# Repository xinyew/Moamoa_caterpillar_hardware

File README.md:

# Caterpillar — Hardware

KiCad project for the **caterpillar** board: a custom nRF54L15-based motor-control + IMU
board (vibration robot). Firmware lives in a sibling repo:
`Moamoa_caterpillar_firmware` (Zephyr / nRF Connect SDK v3.3.0, board target
`caterpillar/nrf54l15/cpuapp`).

## Board overview

| Subsystem    | IC                           | Interface   | Purpose                                     |
| ------------ | ---------------------------- | ----------- | ------------------------------------------- |
| MCU + BLE    | Raytac AN54LQ-P15 (nRF54L15) | —          | Application core + BLE remote control       |
| Motor driver | DRV8212P                     | PWM + GPIO  | Dual-channel motor control                  |
| Digital pot  | MAX5419LETA                  | I2C`0x28` | Adjusts motor supply voltage via STBB1-APUR |
| Buck-boost   | STBB1-APUR                   | GPIO enable | Motor supply rail                           |
| Buck-boost   | ADP2503 (3.3 V)              | —          | Logic supply rail                           |
| IMU          | ASM330LHHTR                  | SPI         | 6-axis accel/gyro                           |
| Inductor     | TDK VLCF4020T-2R2N1R7        | —          | 2.2 µH power inductor                      |

## Pin map (must stay in sync with firmware)

| Signal         | Pin   | Dir   | Notes                               |
| -------------- | ----- | ----- | ----------------------------------- |
| I2C SDA        | P1.02 | bidir | Digipot only (`i2c20`)            |
| I2C SCL        | P1.03 | out   | Digipot only                        |
| IMU INT1       | P1.04 | in    | ASM330LHHTR data-ready              |
| IMU INT2       | P1.05 | in    | ASM330LHHTR secondary interrupt     |
| SPI CS         | P1.09 | out   | ASM330LHHTR chip select, active-low |
| SPI SCLK       | P1.10 | out   | IMU SPI clock                       |
| SPI MOSI       | P1.13 | out   | IMU SPI data out (U2 SDI)           |
| SPI MISO       | P1.14 | in    | IMU SPI data in (U2 SDO)            |
| STATUS LED     | P0.01 | out   | Blue LED via 470R, active-high      |
| DRV8212 ~SLEEP | P1.06 | out   | Active-low sleep (LOW = sleep)      |
| PWM IN1        | P1.07 | out   | Motor driver channel 1 (`pwm20`)  |
| PWM IN2        | P1.08 | out   | Motor driver channel 2              |
| DCDC EN        | P2.03 | out   | STBB1-APUR enable, active-high      |

If you change any of these nets, update the devicetree in the firmware repo
(`boards/kamoamoa/caterpillar/`) and this table.

## Project files

```
caterpillar.kicad_pro   project settings
caterpillar.kicad_sch   schematic
caterpillar.kicad_pcb   PCB layout
caterpillar.csv         BOM export
sym-lib-table           project symbol libraries
fp-lib-table            project footprint libraries
library/                custom components (see rules below)
```

`caterpillar.kicad_prl` and `fp-info-cache` are per-user/cache files and are gitignored.

## Library component organization — the rules

Every custom component lives in its own folder under `library/`, laid out exactly like this:

```
library/<PART>/
  <PART>.kicad_sym          symbol library (named after the part, no dated filenames)
  footprints.pretty/        footprint library (one .kicad_mod per footprint variant)
  <model>.step              3D model (optional)
```

Conventions:

1. **Every footprint links its 3D model.** If the component has a STEP file,
   *each* `.kicad_mod` in `footprints.pretty/` (including -L/-M density variants)
   must contain a `(model ...)` clause pointing to it — otherwise the part renders
   as bare pads in the 3D viewer. Vendor downloads often ship the `.kicad_mod`
   without this clause; add it when importing.
2. **3D model paths are project-relative** — inside a footprint use
   `(model "library/<PART>/<model>.step")`, not `${KIPRJMOD}/...` and never an
   absolute path.
3. **The symbol's Footprint property** must be fully qualified:
   `<fp-lib-nickname>:<footprint-name>`, so placing the symbol auto-assigns
   the footprint.
4. **Register both tables** — add the `.kicad_sym` to `sym-lib-table` and the
   `footprints.pretty/` folder to `fp-lib-table`, both via `${KIPRJMOD}` URIs.
5. **Keep only what KiCad needs.** From vendor downloads (SamacSys/Mouser,
   UltraLibrarian, CSE) copy only the `.kicad_sym`, the `.kicad_mod`(s), and the
   STEP model. Do not commit legacy `.lib`/`.dcm`/`.mod` files, other-CAD folders,
   ImportGuides/readme junk, or the original .zip.

### Importing a new vendor component, step by step

1. `mkdir library/<PART>/footprints.pretty`
2. Copy `<vendor>.kicad_sym` → `library/<PART>/<PART>.kicad_sym`
3. Copy `*.kicad_mod` → `library/<PART>/footprints.pretty/`
4. Copy the `.step`/`.stp` → `library/<PART>/`
5. In the footprint(s), set the model path to `library/<PART>/<model>.step`
6. In the symbol, set the Footprint property to `<PART>:<footprint-name>`
7. Add one entry each to `sym-lib-table` and `fp-lib-table`
8. Verify in KiCad: symbol chooser shows the part, footprint 3D viewer shows the model

## Notes

- Fab history: boards to be ordered.

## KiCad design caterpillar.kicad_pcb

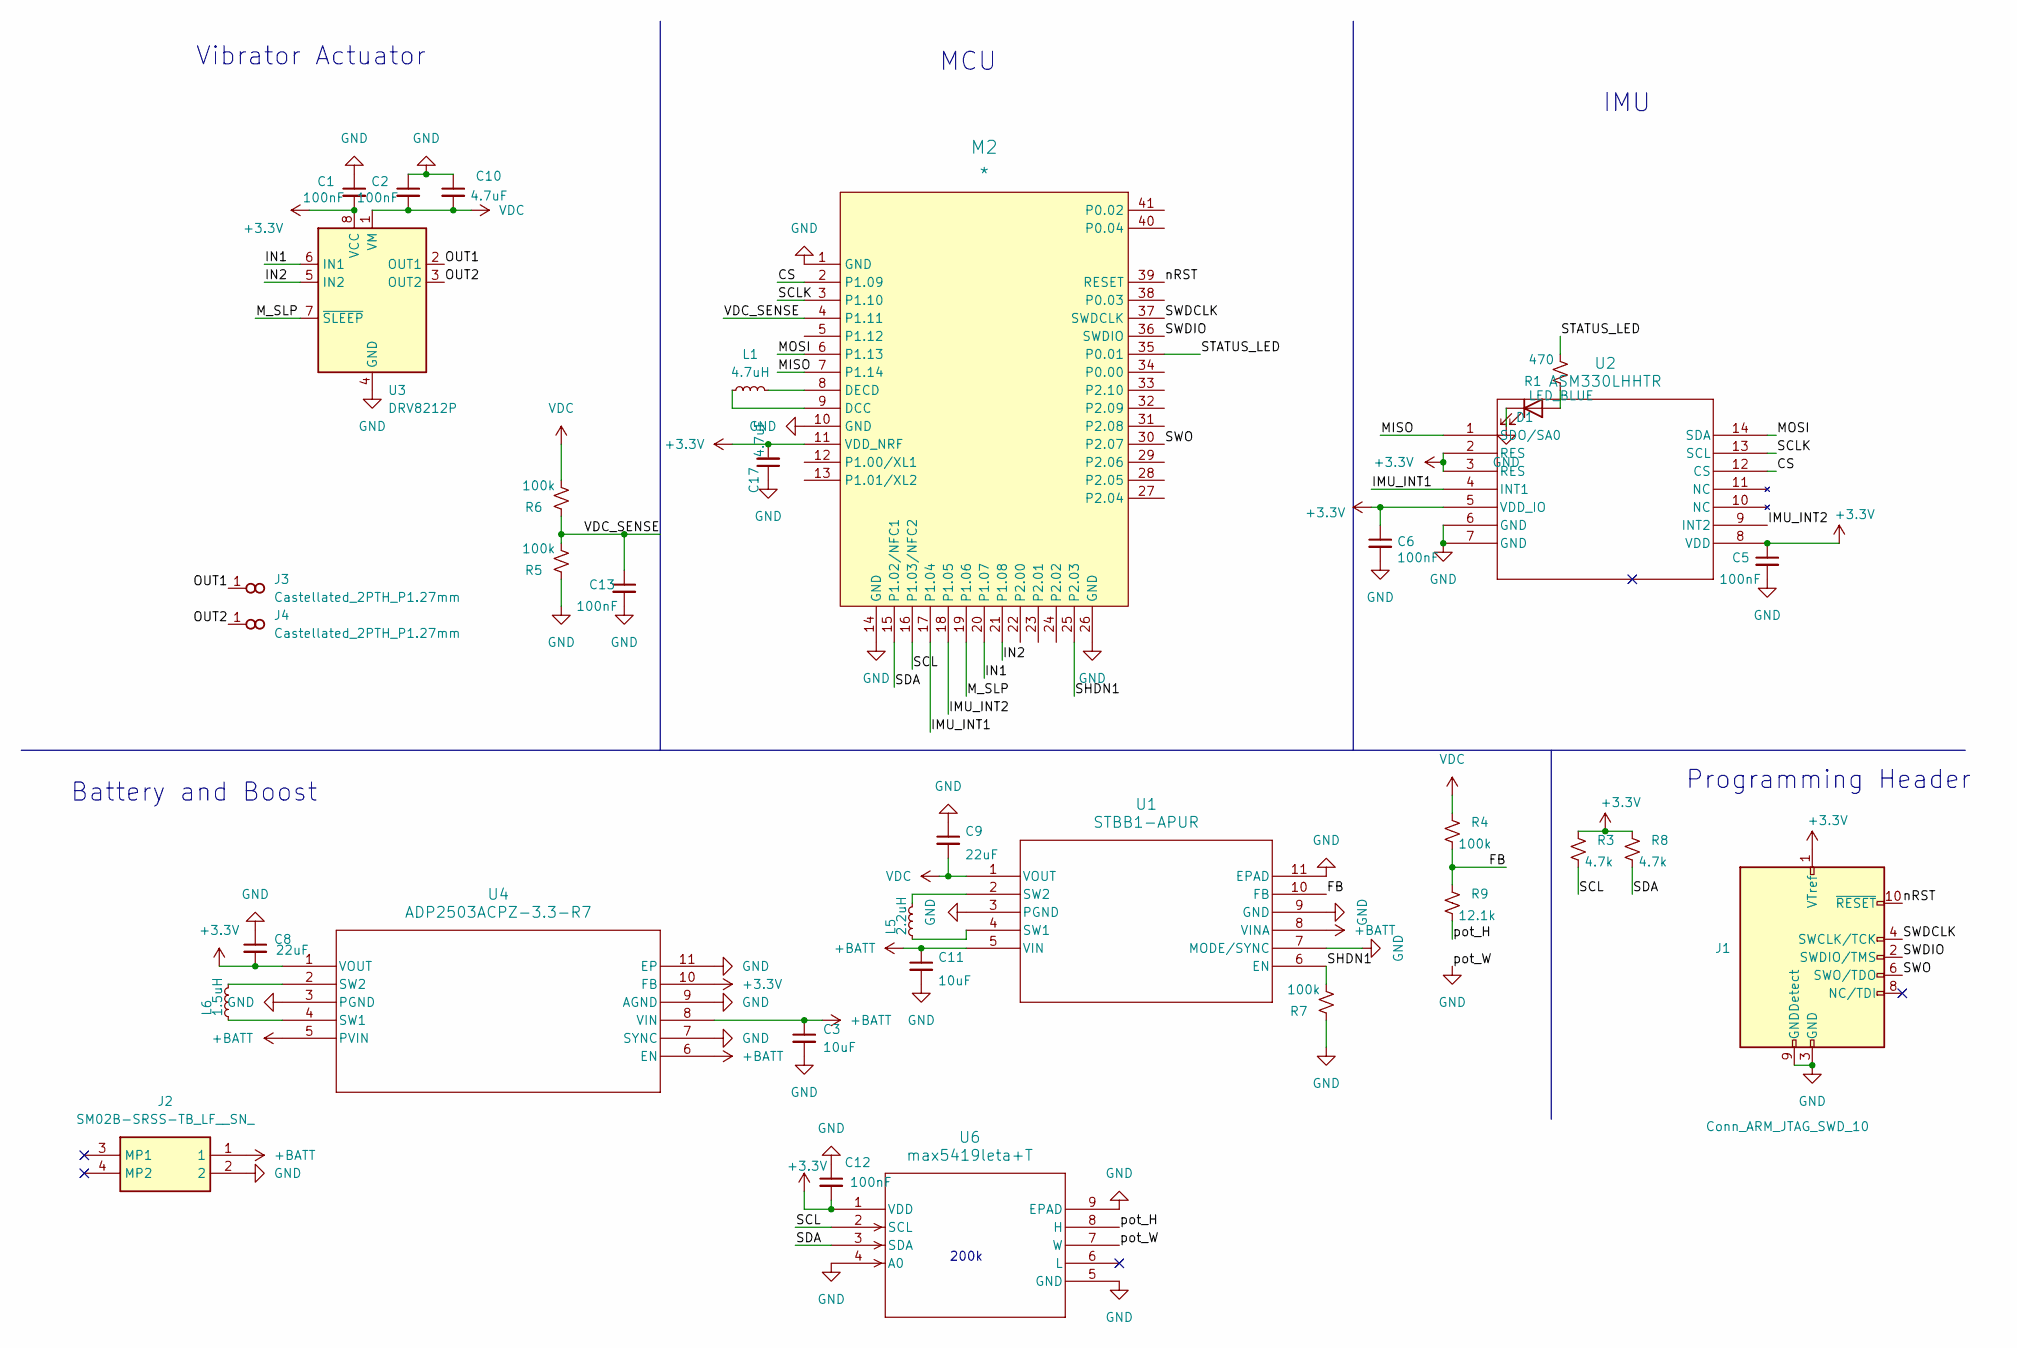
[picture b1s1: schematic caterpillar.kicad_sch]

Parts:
C1, C2, C5, C6, C12, C13: 100nF; C_0603_1608Metric
C3, C11: 10uF; C_0603_1608Metric; MPN GMC10X7R106K10NT
C8, C9: 22uF; C_0603_1608Metric; MPN CL10A226MP8NUNE
C10, C17: 4.7uF; C_0603_1608Metric
D1: LED_BLUE; LED_0603_1608Metric
J1: Conn_ARM_JTAG_SWD_10; PinHeader_2x05_P1.27mm_Vertical_SMD
J2: SM02B-SRSS-TB_LF__SN_; SM02BSRSSTBLFSN; Mouser Part Number N/A
J3, J4: Castellated_2PTH_P1.27mm
L1: 4.7uH; L_0603_1608Metric
L5: 2.2uH; VLCF4020
L6: 1.5uH; L_0603_1608Metric; MPN LSCNB1608HKT1R5MD
M2: *; AN54LQ-P15
R1: 470; R_0603_1608Metric
R3, R8: 4.7k; R_0603_1608Metric
R4, R5, R6, R7: 100k; R_0603_1608Metric
R9: 12.1k; R_0603_1608Metric
U1: STBB1-APUR; SON_B1-APUR_STM-M
U2: ASM330LHHTR; LGA-14L_2P5X3X0P83_STM-L
U3: DRV8212P; WSON-8-1EP_2x2mm_P0.5mm_EP0.9x1.6mm_ThermalVias
U4: ADP2503ACPZ-3.3-R7; CP_10_9_ADI-M
U6: max5419leta+T; 21-0137_T833&plus_2_MXM-M

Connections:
+3.3V: C1.2, C5.1, C6.1, C8.2, C12.2, C17.2, J1.1 (VTref), M2.11 (VDD_NRF), R3.1, R8.1, U2.2 (RES), U2.3 (RES), U2.5 (VDD_IO), U2.8 (VDD), U3.8 (VCC), U4.1 (VOUT), U4.10 (FB), U6.1 (VDD)
+BATT: C3.1, C11.1, J2.1, U1.5 (VIN), U1.8 (VINA), U4.5 (PVIN), U4.6 (EN), U4.8 (VIN)
/CS: M2.2 (P1.09), U2.12 (CS)
/FB: R4.2, R9.1, U1.10 (FB)
/IMU_INT1: M2.17 (P1.04), U2.4 (INT1)
/IMU_INT2: M2.18 (P1.05), U2.9 (INT2)
/IN1: M2.20 (P1.07), U3.6 (IN1)
/IN2: M2.21 (P1.08), U3.5 (IN2)
/MISO: M2.7 (P1.14), U2.1 (SDO/SA0)
/MOSI: M2.6 (P1.13), U2.14 (SDA)
/M_SLP: M2.19 (P1.06), U3.7 (~SLEEP)
/OUT1: J3.1 (~_1), U3.2 (OUT1)
/OUT2: J4.1 (~_1), U3.3 (OUT2)
/SCL: M2.16 (P1.03/NFC2), R3.2, U6.2 (SCL)
/SCLK: M2.3 (P1.10), U2.13 (SCL)
/SDA: M2.15 (P1.02/NFC1), R8.2, U6.3 (SDA)
/SHDN1: M2.25 (P2.03), R7.2, U1.6 (EN)
/STATUS_LED: M2.35 (P0.01), R1.2
/SWDCLK: J1.4 (SWCLK/TCK), M2.37 (SWDCLK)
/SWDIO: J1.2 (SWDIO/TMS), M2.36 (SWDIO)
/SWO: J1.6 (SWO/TDO), M2.30 (P2.07)
/VDC_SENSE: C13.1, M2.4 (P1.11), R5.2, R6.1
/nRST: J1.10 (~RESET), M2.39 (RESET)
/pot_H: R9.2, U6.8 (H)
GND: C1.1, C2.1, C3.2, C5.2, C6.2, C8.1, C9.1, C10.1, C11.2, C12.1, C13.2, C17.1, D1.1 (K), J1.3 (GND), J1.5 (GND), J1.9 (GNDDetect), J2.2, M2.1 (GND), M2.10 (GND), M2.14 (GND), M2.26 (GND), R5.1, R7.1, U1.3 (PGND), U1.7 (MODE/SYNC), U1.9 (GND), U1.11 (EPAD), U2.6 (GND), U2.7 (GND), U3.4 (GND), U3.9 (GND), U4.3 (PGND), U4.7 (SYNC), U4.9 (AGND), U4.11 (EP), U6.4 (A0), U6.5 (GND), U6.7 (W), U6.9 (EPAD)
unnamed: D1.2 (A), R1.1
unnamed: L1.1, M2.9 (DCC)
unnamed: L1.2, M2.8 (DECD)
unnamed: L5.1, U1.4 (SW1)
unnamed: L5.2, U1.2 (SW2)
unnamed: L6.1, U4.4 (SW1)
unnamed: L6.2, U4.2 (SW2)
VDC: C2.2, C9.2, C10.2, R4.1, R6.2, U1.1 (VOUT), U3.1 (VM)

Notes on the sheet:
Vibrator Actuator
MCU
IMU
Battery and Boost
Programming Header
200k

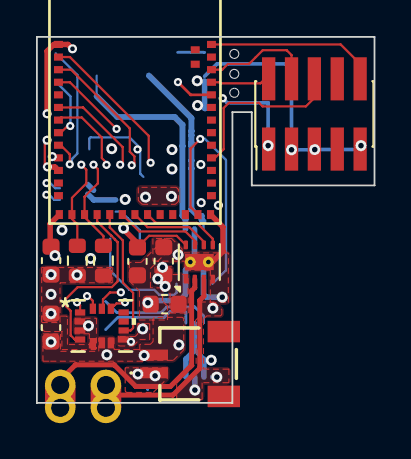
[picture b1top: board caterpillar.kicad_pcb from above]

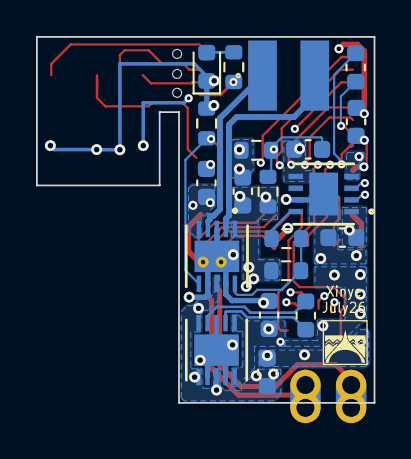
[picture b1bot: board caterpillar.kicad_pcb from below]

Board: 4 copper layers, 18.8 x 20.3 mm, 34 parts (20 on the bottom side), 33 nets.
